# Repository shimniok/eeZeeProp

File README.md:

eeZeeProp is an affordable breadboard breakout for Parallax Propeller featuring FTDI and PropPlug programming ports, all
GPIO pins broken out, configurable BOE, and flexible power supply options.  It has onboard crystal, regulator, EEPROM,
and current limiting resistors on the serial programming pins.

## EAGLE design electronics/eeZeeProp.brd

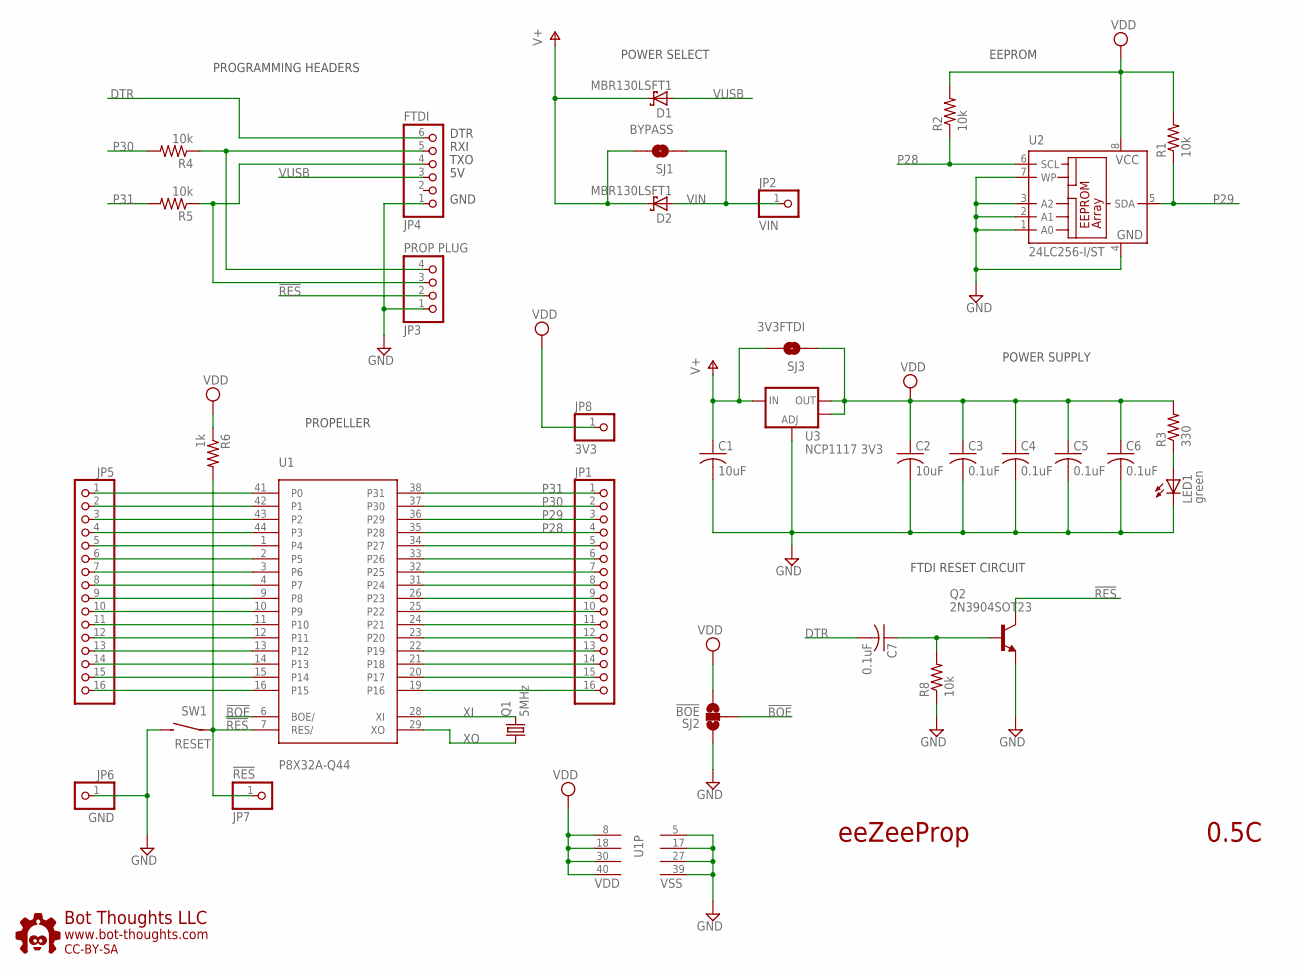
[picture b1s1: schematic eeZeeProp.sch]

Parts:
C1, C2: 10uF; C1206; PARTNO T491A106M006AT
C3, C4, C5, C6, C7: 0.1uF; C0603; PARTNO 0603YC104KAT2A
D1, D2: MBR130LSFT1; SOD123FL; PARTNO MBR130LSFT1G
JP1, JP5: PINHD-1X16_2.54-S; 1X16-S
JP2: VIN; 1X01
JP3: PROP PLUG; 1X04-S
JP4: FTDI; 1X06-S; PARTNO 2211S-06G
JP6: GND; 1X01
JP7: !RES; 1X01
JP8: 3V3; 1X01
LED1: green; CHIPLED_1206; PARTNO LG N971-KN-1
Q1: 5MHz; HC49U-V; PARTNO HC49US-5.000MABJ-UB
Q2: 2N3904SOT23; SOT-23; PARTNO MMBT3904LT3G
R1, R2, R8: 10k; R0603; PARTNO ERJ-3GEYJ103V
R3: 330; R0603; PARTNO ERJ-3GEYJ331V
R4, R5: 10k; R0603; PARTNO RC0603JR-071KL
R6: 1k; R0603; PARTNO RC0603JR-071KL
SJ1: BYPASS; SJ_2S-NO
SJ2: !BOE; SJ_3
SJ3: 3V3FTDI; SJ_2S-NO
SW1: RESET; 6MMTACTILE_RECT; PARTNO MJTP1243
U1: P8X32A-Q44; PARTNO P8X32A-Q44
U2: 24LC256-I/ST; SO-08; MPN CAT24C256WI-GT3
U3: NCP1117 3V3; SOT223; PARTNO NCP1117ST33T3G
U$1: BTLOGO-LOGO-MD; BTLOGOM

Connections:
!BOE: SJ2.2, U1.6 (BOE/)
!RES: JP3.2, JP7.1, Q2.1 (C), R6.2, SW1.P$1, U1.7 (RES/)
DTR: C7.2, JP4.6
GND: C1.2, C2.2, C3.2, C4.2, C5.2, C6.2, JP3.1, JP4.1, JP6.1, LED1.C, Q2.2 (E), R8.1, SJ2.1, SW1.P$2 (S), U1.5 (VSS), U1.17 (VSS), U1.27 (VSS), U1.39 (VSS), U2.1 (A0), U2.2 (A1), U2.3 (A2), U2.4 (GND), U2.7 (WP), U3.1 (ADJ)
unnamed: JP5.1, U1.41 (P0)
unnamed: JP5.2, U1.42 (P1)
unnamed: JP5.3, U1.43 (P2)
unnamed: JP5.4, U1.44 (P3)
unnamed: LED1.A, R3.1
unnamed: JP5.5, U1.1 (P4)
unnamed: JP5.6, U1.2 (P5)
unnamed: JP5.7, U1.3 (P6)
unnamed: JP5.8, U1.4 (P7)
unnamed: JP5.9, U1.9 (P8)
unnamed: JP5.10, U1.10 (P9)
unnamed: JP5.11, U1.11 (P10)
unnamed: JP5.12, U1.12 (P11)
unnamed: JP5.13, U1.13 (P12)
unnamed: JP5.14, U1.14 (P13)
unnamed: JP5.15, U1.15 (P14)
unnamed: JP5.16, U1.16 (P15)
unnamed: JP1.5, U1.34 (P27)
unnamed: JP1.6, U1.33 (P26)
unnamed: JP1.7, U1.32 (P25)
unnamed: JP1.8, U1.31 (P24)
unnamed: JP1.9, U1.26 (P23)
unnamed: JP1.10, U1.25 (P22)
unnamed: JP1.11, U1.24 (P21)
unnamed: JP1.12, U1.23 (P20)
unnamed: JP1.13, U1.22 (P19)
unnamed: JP1.14, U1.21 (P18)
unnamed: JP1.15, U1.20 (P17)
unnamed: JP1.16, U1.19 (P16)
unnamed: C7.1, Q2.3 (B), R8.2
P28: JP1.4, R2.1, U1.35 (P28), U2.6 (SCL)
P29: JP1.3, R1.1, U1.36 (P29), U2.5 (SDA)
P30: JP1.2, R4.2, U1.37 (P30)
P31: JP1.1, R5.2, U1.38 (P31)
RXI: JP3.4, JP4.5, R4.1
TXO: JP3.3, JP4.4, R5.1
V+: C1.1, D1.C, D2.C, SJ1.2, SJ3.2, U3.3 (IN)
VDD: C2.1, C3.1, C4.1, C5.1, C6.1, JP8.1, R1.2, R2.2, R3.2, R6.1, SJ2.3, SJ3.1, U1.8 (VDD), U1.18 (VDD), U1.30 (VDD), U1.40 (VDD), U2.8 (VCC), U3.2 (OUT), U3.4 (OUT)
VIN: D2.A, JP2.1, SJ1.1
VUSB: D1.A, JP4.3
XI: Q1.2, U1.28 (XI)
XO: Q1.1, U1.29 (XO)

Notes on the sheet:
!BOE
eeZeeProp
0.5C
RXI
TXO
DTR
GND
FTDI RESET CIRCUIT
POWER SUPPLY
POWER SELECT
PROGRAMMING HEADERS
EEPROM
PROPELLER

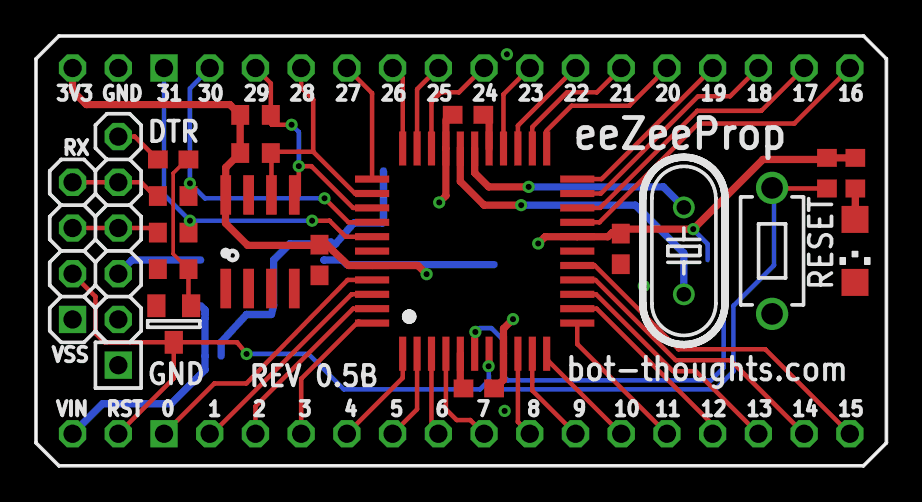
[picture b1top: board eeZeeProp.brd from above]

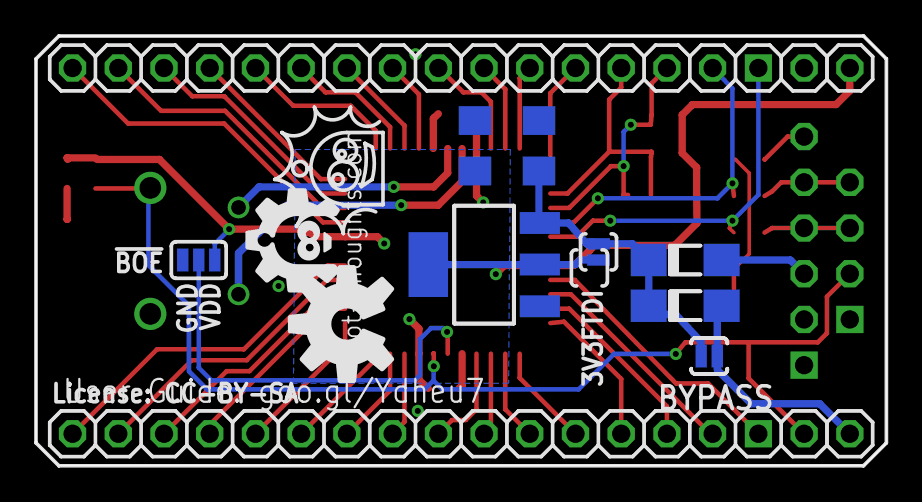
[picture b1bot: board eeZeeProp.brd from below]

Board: 2 copper layers, 47.2 x 23.9 mm, 35 parts (15 on the bottom side), 46 nets.

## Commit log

2012-11-23 Revision 0.2
2012-12-11 Rev 0.2 as built
2012-12-28 Revised reset circuit, added bypass for VIN diode, added BOE solder jumper
2013-01-02 Rev 0.3 as-ordered
2013-01-29 Enlarged pads for SOT-23 and SOD123F for easier hand assembly. Slight tweaks to traces.
2013-02-04 Minor layout tweaks
2013-06-14 Fixes to PropVGA, microSD,
2013-08-06 Version 0.4, changes some footprints for easier rework, some mods to routing, mitered corners, some other stuff I'm forgetting.
2013-10-25 Renamed microSD files, moved to electronics subfolder
2013-11-11 Adding firmware examples into subdirectory. Moving electronics cad into electronics directory.
2013-12-11 Added regulator bypass option for 3.3V FTDI. Increased diode pad sizes.
2014-02-04 Fixed silkscreen conflicts. Enlarged DTR/GND labels. Moved other silk labels to different layer, disabled bottom name silk gen.
2014-04-15 Revised diode placement, silk, pin 1 dot on propeller.
2014-10-17 Changed to 8mil spacing, revised all PTH pins to octagon, relocated traces, vias for clearance. Resized traces with clearance problems.
2014-11-08 Removed some test files, added PinTester back
2015-04-24 updated gerbers for latest production run
2015-04-24 Changed delay
2015-04-24 removed eagle.epf
2015-04-24 consolidated eeZeeProp test/firmware/examples
2015-04-24 renamed eeZeeProp directory
2015-05-05 Removed 3rd party demo programs, added license files
2015-05-05 moved zip
2015-05-05 added README
2015-11-12 Added documentation, migrated from google code
2015-11-16 added images for documentation
2015-11-16 shrunk pic
2015-11-16 Updated readme, reorganized, changed pictures to local
2015-11-16 renamed firmware to examples
2015-11-16 Added links/resources
2015-11-16 added solder jumper pic
2015-11-16 added pic for solder jumpers
2017-03-19 Revised silkscreen labels, added user guide link, minor relocation of 3v3 ftdi solder jumper and label, updated bt logo
2021-02-10 added description file

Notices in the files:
electronics/eeZeeProp.brd:
CC-BY-SA
License: CC-BY-SA
